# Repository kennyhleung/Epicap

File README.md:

# Epicap
EEG baseball cap with camera for seizure activity monitoring
ADS1299-raspberry pi module that connects to Raspberry Pi Zero W 2 (can be to other RPis)

## Acknowledgements
RaspberryPi ADS1299 driver from https://github.com/wjcroft/RaspberryPiADS1299

## Connections
Connect additional electrode wires to SRB2 and BIAS (reference: https://docs.openbci.com/GettingStarted/Biosensing-Setups/EEGSetup/)

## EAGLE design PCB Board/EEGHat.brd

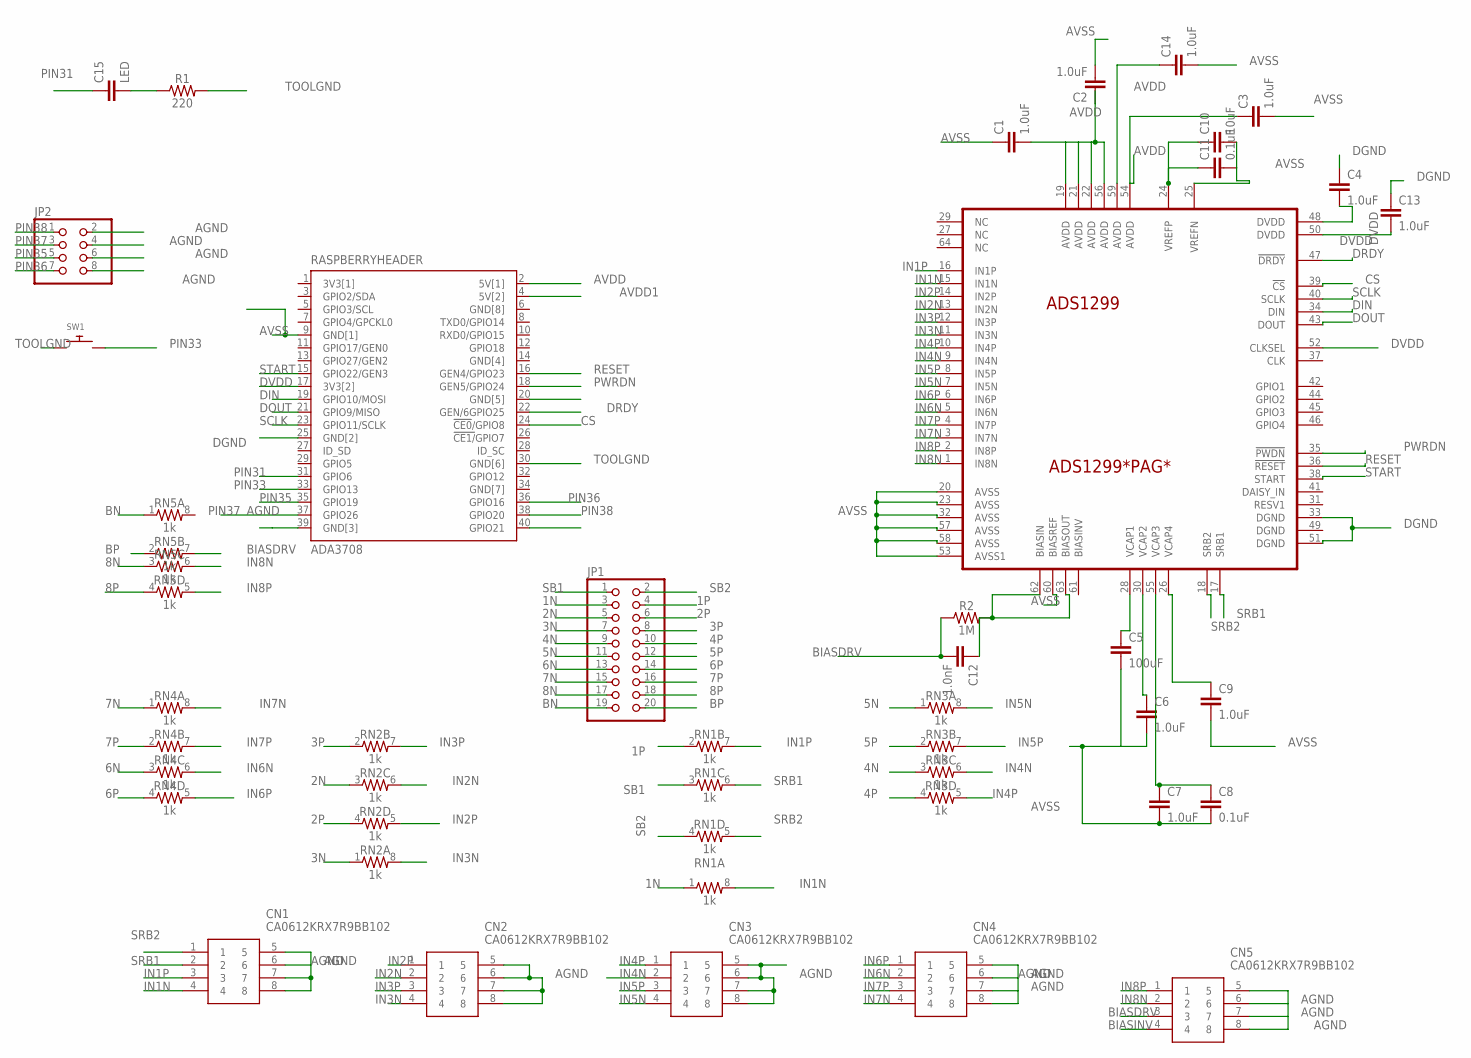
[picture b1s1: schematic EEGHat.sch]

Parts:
ADS1299: ADS1299*PAG*; TQFP64
C1, C2, C3, C4, C6, C7, C9, C13, C14: 1.0uF; 0805
C5: 100uF; 0805
C8, C11: 0.1uF; 0805
C10: 10uF; 0805
C12: 1.0nF; 0805
C15: LED; 0805
CN1, CN2, CN3, CN4, CN5: CA0612KRX7R9BB102
JP1: PINHD-2X10; 2X10
JP2: PINHD-2X4; 2X04
R1: 220; 0805
R2: 1M; 0805
RASPBERRYHEADER: ADA3708; ADA3708_RPI-ZERO
RN1, RN2, RN3, RN4, RN5: 1k; 0805-ARV
SW1: SWITCH_PUSHBUTTONSOFTTOUCHSMD_SJ; PUSHBUTTON_SMD_SJ

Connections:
1N: JP1.3, RN1.1
1P: JP1.4, RN1.2 (1)
2N: JP1.5, RN2.3 (1)
2P: JP1.6, RN2.4 (1)
3N: JP1.7, RN2.1
3P: JP1.8, RN2.2 (1)
3V3[1]: RASPBERRYHEADER.1 (3V3[1])
4N: JP1.9, RN3.3 (1)
4P: JP1.10, RN3.4 (1)
5N: JP1.11, RN3.1
5P: JP1.12, RN3.2 (1)
6N: JP1.13, RN4.3 (1)
6P: JP1.14, RN4.4 (1)
7N: JP1.15, RN4.1
7P: JP1.16, RN4.2 (1)
8N: JP1.17, RN5.3 (1)
8P: JP1.18, RN5.4 (1)
AGND: CN1.5, CN1.6, CN1.7, CN1.8, CN2.5, CN2.6, CN2.7, CN2.8, CN3.5, CN3.6, CN3.7, CN3.8, CN4.5, CN4.6, CN4.7, CN4.8, CN5.5, CN5.6, CN5.7, CN5.8, JP2.2, JP2.4, JP2.6, JP2.8, RASPBERRYHEADER.39 (GND[3])
AVDD: ADS1299.19 (AVDD), ADS1299.21 (AVDD), ADS1299.22 (AVDD), ADS1299.54 (AVDD), ADS1299.56 (AVDD), ADS1299.59 (AVDD), C1.2, C2.1, C3.1, C14.1, RASPBERRYHEADER.2 (5V[1])
AVDD1: RASPBERRYHEADER.4 (5V[2])
AVSS: ADS1299.20 (AVSS), ADS1299.23 (AVSS), ADS1299.25 (VREFN), ADS1299.32 (AVSS), ADS1299.53 (AVSS1), ADS1299.57 (AVSS), ADS1299.58 (AVSS), ADS1299.60 (BIASREF), C1.1, C2.2, C3.2, C5.2, C6.2, C7.2, C8.2, C9.2, C10.2, C11.2, C14.2, RASPBERRYHEADER.9 (GND[1])
BIASDRV: C12.2, CN5.3, R2.1, RN5.7 (2)
BIASINV: CN5.4
BN: JP1.19, RN5.1
BP: JP1.20, RN5.2 (1)
CS: ADS1299.39 (!CS), RASPBERRYHEADER.24 (!CE0!/GPIO8)
DGND: ADS1299.33 (DGND), ADS1299.49 (DGND), ADS1299.51 (DGND), C4.1, C13.1, RASPBERRYHEADER.25 (GND[2])
DIN: ADS1299.34 (DIN), RASPBERRYHEADER.19 (GPIO10/MOSI)
DOUT: ADS1299.43 (DOUT), RASPBERRYHEADER.21 (GPIO9/MISO)
DRDY: ADS1299.47 (!DRDY), RASPBERRYHEADER.22 (GEN/6GPIO25)
DVDD: ADS1299.48 (DVDD), ADS1299.50 (DVDD), ADS1299.52 (CLKSEL), C4.2, C13.2, RASPBERRYHEADER.17 (3V3[2])
GND[4]: RASPBERRYHEADER.14 (GND[4])
GND[7]: RASPBERRYHEADER.34 (GND[7])
GND[8]: RASPBERRYHEADER.6 (GND[8])
IN1N: ADS1299.15 (IN1N), CN1.4, RN1.8 (2)
IN1P: ADS1299.16 (IN1P), CN1.3, RN1.7 (2)
IN2N: ADS1299.13 (IN2N), CN2.2, RN2.6 (2)
IN2P: ADS1299.14 (IN2P), CN2.1, RN2.5 (2)
IN3N: ADS1299.11 (IN3N), CN2.4, RN2.8 (2)
IN3P: ADS1299.12 (IN3P), CN2.3, RN2.7 (2)
IN4N: ADS1299.9 (IN4N), CN3.2, RN3.6 (2)
IN4P: ADS1299.10 (IN4P), CN3.1, RN3.5 (2)
IN5N: ADS1299.7 (IN5N), CN3.4, RN3.8 (2)
IN5P: ADS1299.8 (IN5P), CN3.3, RN3.7 (2)
IN6N: ADS1299.5 (IN6N), CN4.2, RN4.6 (2)
IN6P: ADS1299.6 (IN6P), CN4.1, RN4.5 (2)
IN7N: ADS1299.3 (IN7N), CN4.4, RN4.8 (2)
IN7P: ADS1299.4 (IN7P), CN4.3, RN4.7 (2)
IN8N: ADS1299.1 (IN8N), CN5.2, RN5.6 (2)
IN8P: ADS1299.2 (IN8P), CN5.1, RN5.5 (2)
unnamed: ADS1299.62 (BIASIN), ADS1299.63 (BIASOUT), C12.1, R2.2
unnamed: ADS1299.28 (VCAP1), C5.1
unnamed: ADS1299.24 (VREFP), C10.1, C11.1
unnamed: C15.2, R1.1
unnamed: ADS1299.30 (VCAP2), C6.1
unnamed: ADS1299.55 (VCAP3), C7.1, C8.1
unnamed: ADS1299.26 (VCAP4), C9.1
PIN31: C15.1, RASPBERRYHEADER.31 (GPIO6)
PIN33: RASPBERRYHEADER.33 (GPIO13), SW1.P$2
PIN35: JP2.5, RASPBERRYHEADER.35 (GPIO19)
PIN36: JP2.7, RASPBERRYHEADER.36 (GPIO16)
PIN37: JP2.3, RASPBERRYHEADER.37 (GPIO26)
PIN38: JP2.1, RASPBERRYHEADER.38 (GPIO20)
PWRDN: ADS1299.35 (!PWDN), RASPBERRYHEADER.18 (GEN5/GPIO24)
RESET: ADS1299.36 (!RESET), RASPBERRYHEADER.16 (GEN4/GPIO23)
SB1: JP1.1, RN1.3 (1)
SB2: JP1.2, RN1.4 (1)
SCLK: ADS1299.40 (SCLK), RASPBERRYHEADER.23 (GPIO11/SCLK)
SRB1: ADS1299.17 (SRB1), CN1.2, RN1.6 (2)
SRB2: ADS1299.18 (SRB2), CN1.1, RN1.5 (2)
START: ADS1299.38 (START), RASPBERRYHEADER.15 (GPIO22/GEN3)
TOOLGND: R1.2, RASPBERRYHEADER.30 (GND[6]), SW1.P$1

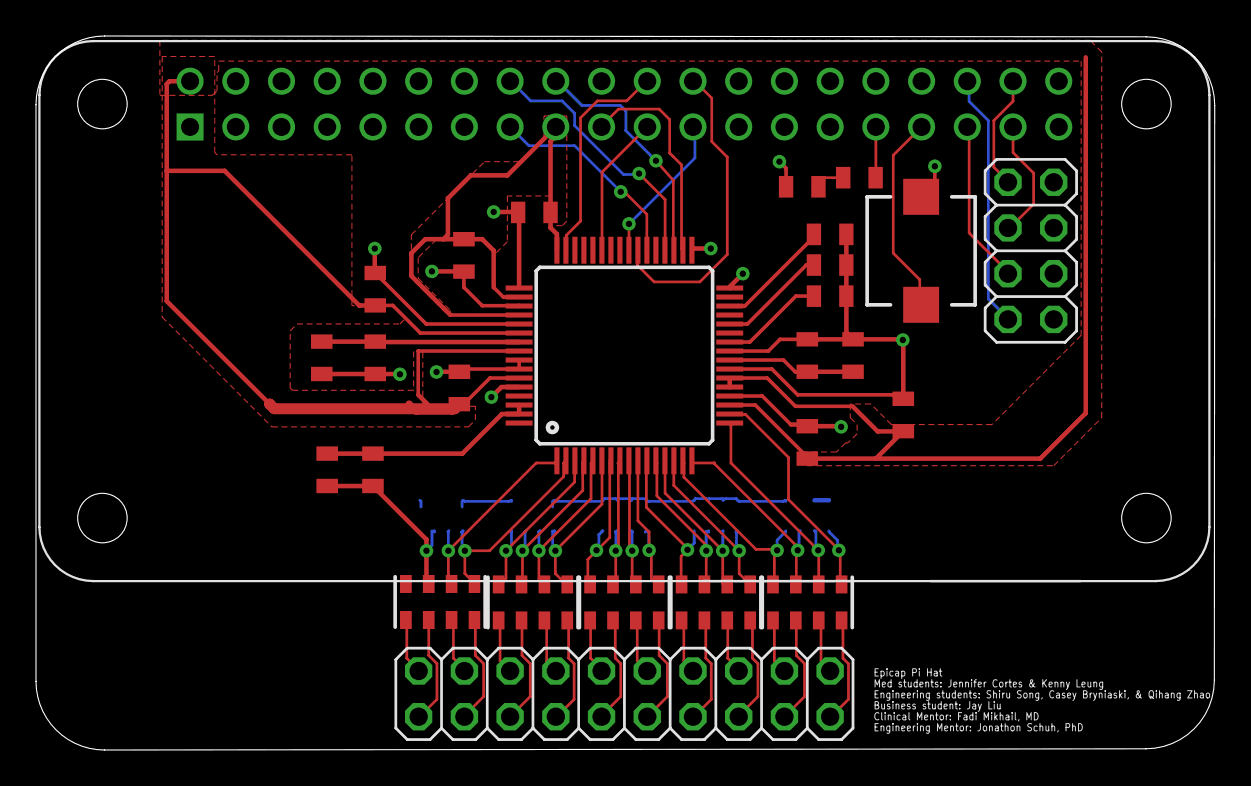
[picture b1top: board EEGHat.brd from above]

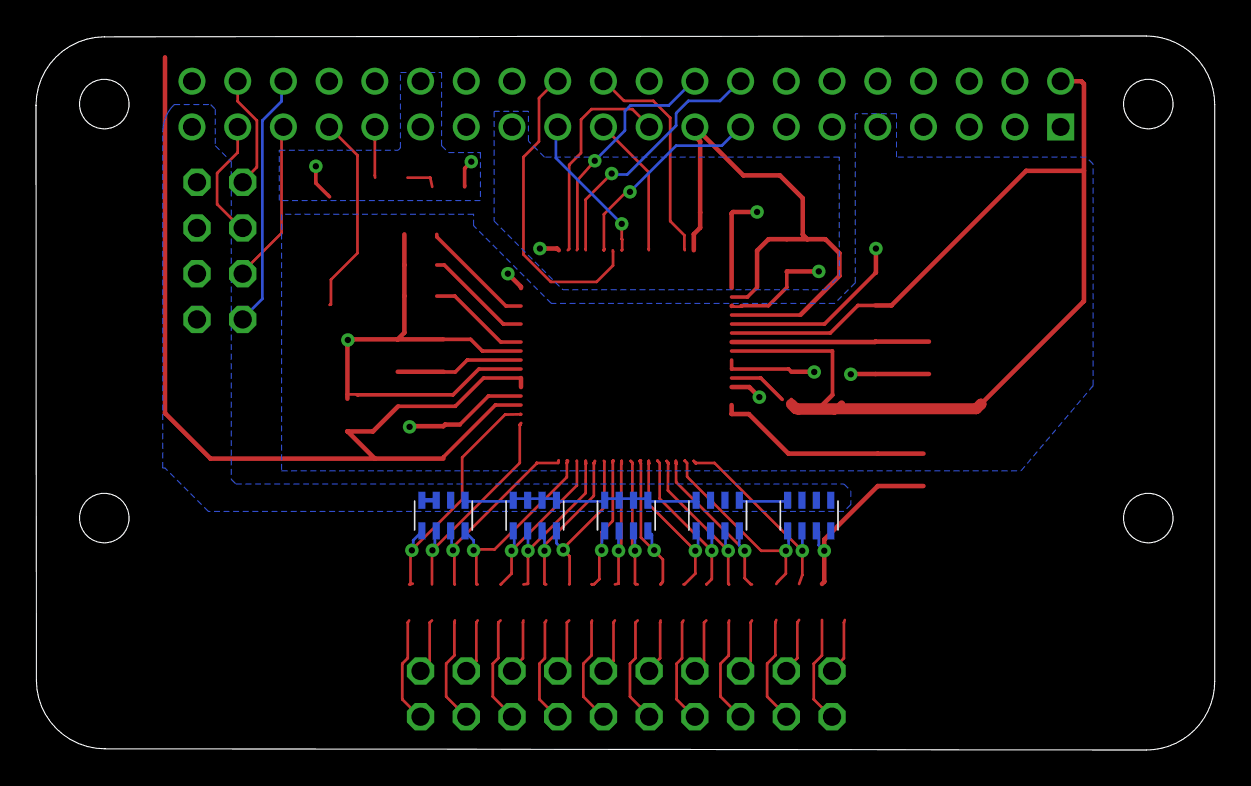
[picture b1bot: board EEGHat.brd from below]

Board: 2 copper layers, 65.5 x 39.7 mm, 32 parts (5 on the bottom side), 66 nets.

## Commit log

2022-01-24 Initial Commit
    3D models and PCB board

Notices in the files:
parts and their libraries:
SparkFun-Capacitors: Licensing: Creative Commons ShareAlike 4.0 International - https://creativecommons.org/licenses/by-sa/4.0
